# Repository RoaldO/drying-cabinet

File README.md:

# clean-air-cabinet

A clean-air cabinet for airbrushed / freshly painted workpieces: an ESP32-driven
extraction fan pulling through a printed duct and foam filter, controlled from
Home Assistant.

One project, three disciplines:

| Folder | What | Tooling |
|---|---|---|
| `cad/` | Parametric fan duct, filter enclosure, finger-guard grill, dust cover, gaskets | build123d (uv), exported as STL/3MF |
| `pcb/` | Carrier board for the ESP32 fan controller — 12 V in, PTC polyfuse, Recom R-78B5.0 buck to 5 V | KiCad |
| `firmware/` | Fan on/off + PWM speed + tach RPM readback, native HA API | ESPHome |

See `docs/2026-08-22-cleanaircabinet-design.md` for the full electronics design
(wiring, GPIO assignment, assumptions) and `cad/` for the material rationale
(PETG over PETG-CF).

## Physical build status (2026-08-28)

Printed and assembled onto a repurposed storage bin; fan runs quietly at ~30–35 %.
Firmware MVP works (on/off + speed from HA, RPM readback). Environmental sensors
deferred — solvent vapour and paint aerosol degrade the candidate sensors.

## Firmware setup

```bash
cd firmware
just secrets                 # sops -d secrets.enc.yaml > secrets.yaml
esphome run cleanaircabinet.yaml   # first flash over USB, then OTA
```

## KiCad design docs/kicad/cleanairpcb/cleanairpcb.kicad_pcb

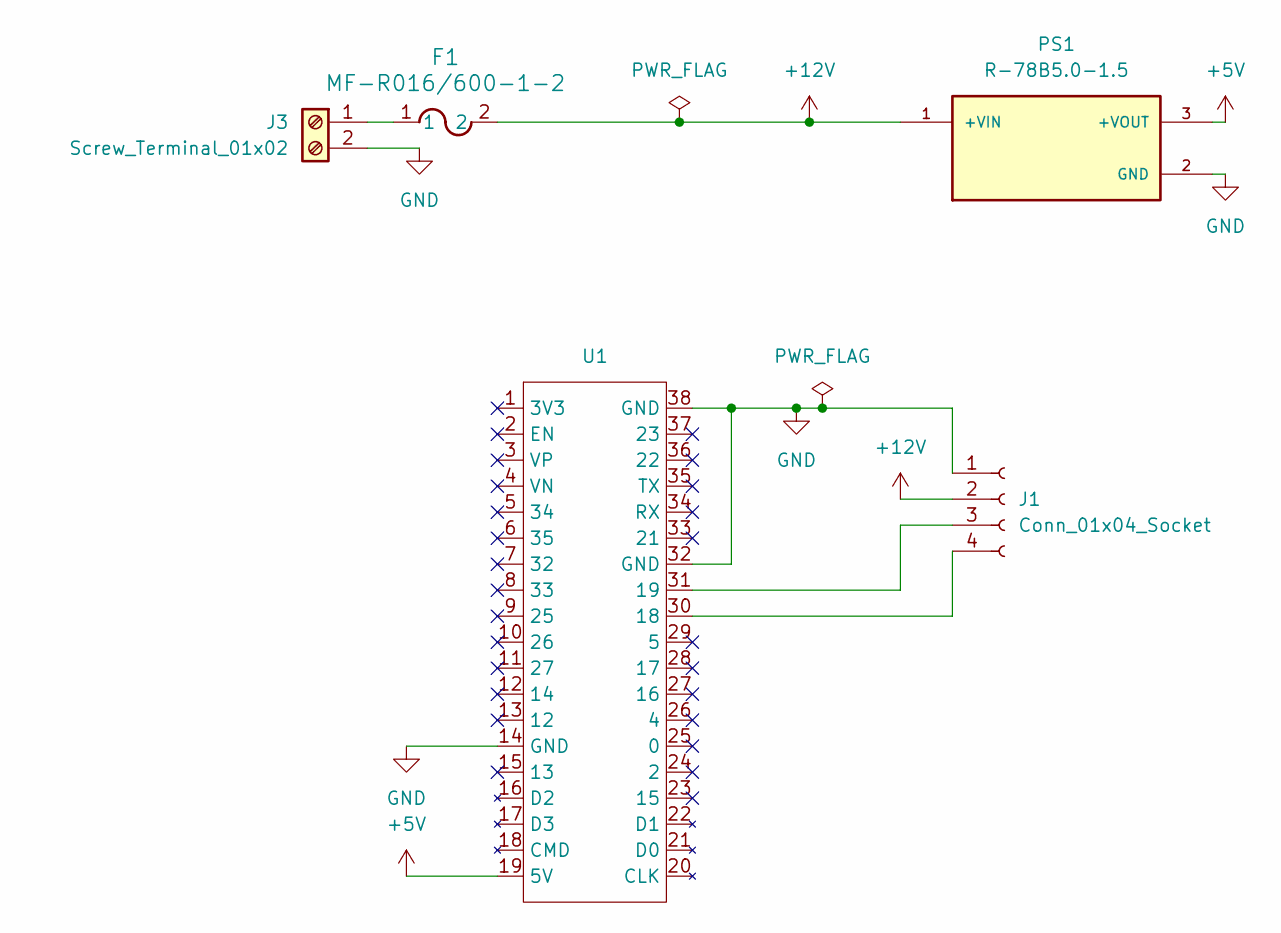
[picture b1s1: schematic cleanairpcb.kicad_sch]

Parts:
F1: MF-R016/600-1-2; FUSE_MFR16_16X6_BRN
J1: Conn_01x04_Socket; JST_XH_B4B-XH-A_1x04_P2.50mm_Vertical
J3: Screw_Terminal_01x02; TerminalBlock_Phoenix_MPT-0,5-2-2.54_1x02_P2.54mm_Horizontal
PS1: R-78B5.0-1.5; SIP3_11.6x8.5mm; PARTREV 4
U1: ESP32_DevKitC_V4

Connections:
+5V: PS1.3 (+VOUT), U1.19 (5V)
+12V: F1.2, J1.2, PS1.1 (+VIN)
GND: J1.1, J3.2, PS1.2 (GND), U1.14 (GND), U1.32 (GND), U1.38 (GND)
unnamed: J1.3, U1.31 (19)
unnamed: J1.4, U1.30 (18)
unnamed: F1.1, J3.1

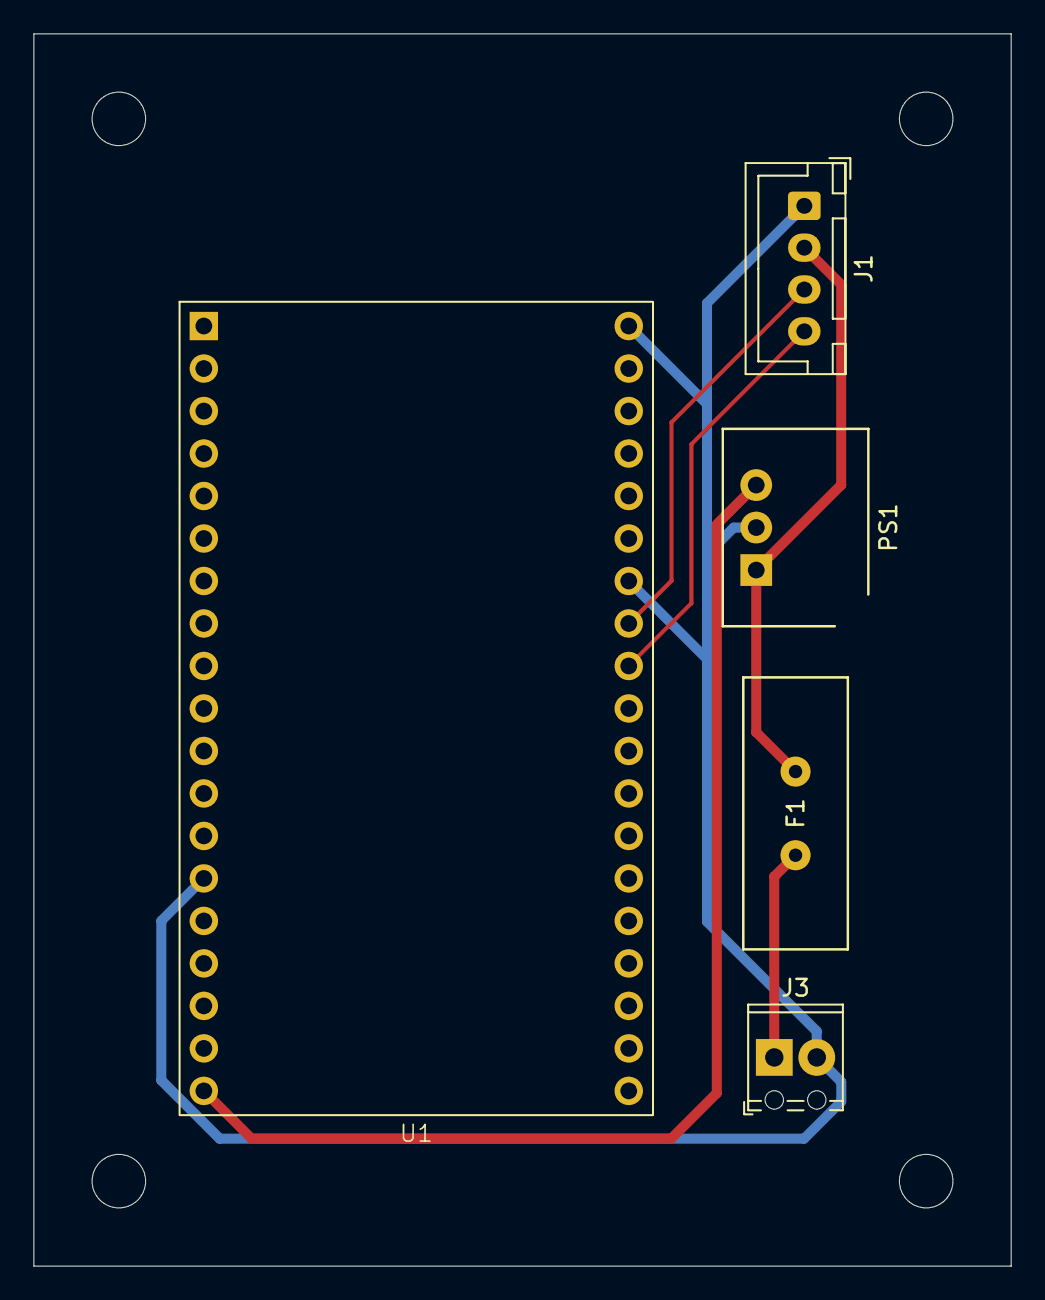
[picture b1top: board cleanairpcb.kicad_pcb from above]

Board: 2 copper layers, 58.4 x 73.7 mm, 5 parts (0 on the bottom side), 6 nets.
